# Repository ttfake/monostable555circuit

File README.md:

Monostable 555 Timer with power switch. Intended to be triggered by external digital signal

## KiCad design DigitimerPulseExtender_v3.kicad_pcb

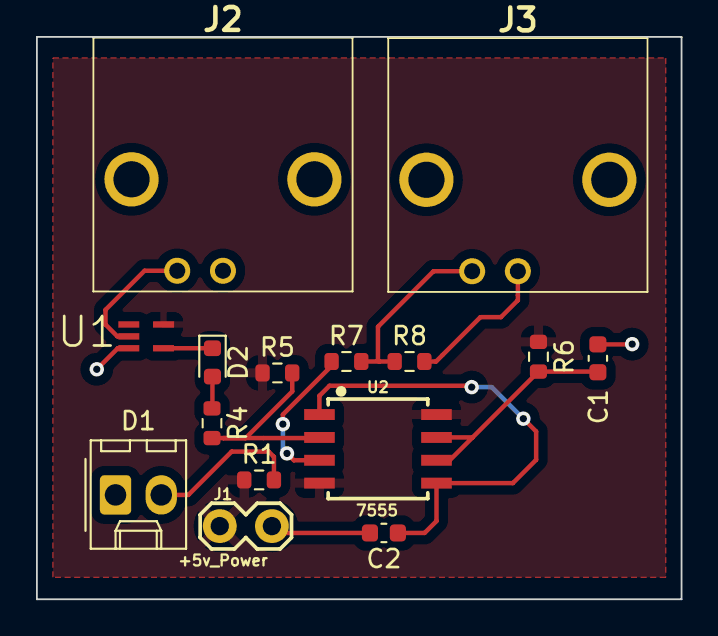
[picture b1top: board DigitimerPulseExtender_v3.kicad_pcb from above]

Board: 2 copper layers, 35.8 x 31.2 mm, 15 parts (0 on the bottom side), 11 nets.

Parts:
C1: 0.1u; C_0603_1608Metric
C2: 0.01u; C_0603_1608Metric
D1: LED; Molex_KK-254_AE-6410-02A_1x02_P2.54mm_Vertical
D2: DIODE-1N4148; D_0603_1608Metric
J1: +5v_Power; 1X02_LOCK
J2: Input_from_DS8R; 031543110RFX
J3: Output_to_DAQ; 031543110RFX
R1: 2k; R_0603_1608Metric
R4, R5, R7, R8: 1k; R_0603_1608Metric
R6: 100k; R_0603_1608Metric
U1: 74HCT1G14GW; SOT65P210X110-5N
U2: 7555; SOIC-8

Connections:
+5V: J1.1, R1.1, R5.1, R6.1, U1.5 (VCC), U2.4 (RES), U2.8 (VCC+)
GND: C1.2, C2.2, D1.1 (K), J1.2, J2.2 (Ext), J3.2 (Ext), R8.2, U1.3 (GND)
unnamed: C1.1, R6.2, U2.6 (TRE), U2.7 (DIS)
unnamed: C2.1, U2.1 (GND), U2.5 (CON)
unnamed: D1.2 (A), R1.2
unnamed: D2.A, U1.4 (Y)
unnamed: D2.B, R4.1
unnamed: R4.2, R5.2, U2.2 (TRI)
unnamed: R7.1, U2.3 (OUT)
Output_Pin_3_R7_R8: J3.1 (In), R7.2, R8.1
Pin_2_on_Inverter: J2.1 (In), U1.2 (A)

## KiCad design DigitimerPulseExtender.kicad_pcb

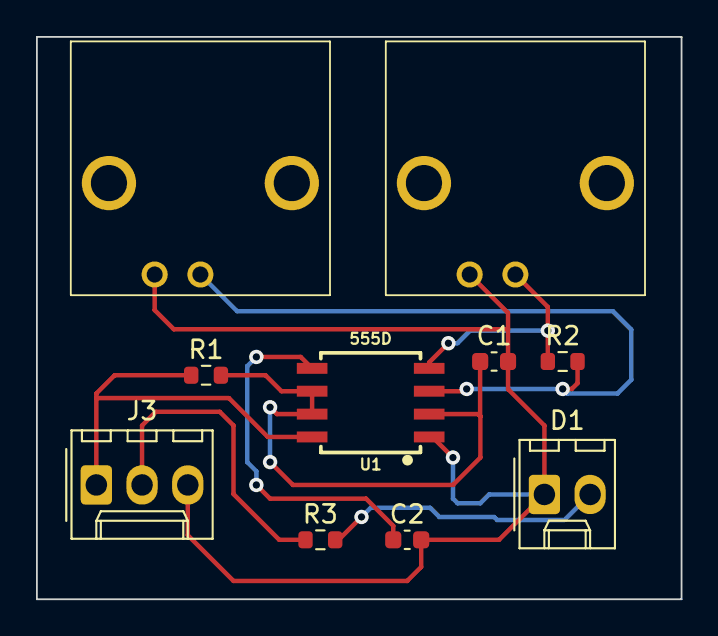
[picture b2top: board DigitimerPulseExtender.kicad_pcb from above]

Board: 2 copper layers, 35.8 x 31.2 mm, 10 parts (0 on the bottom side), 8 nets.

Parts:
C1: 0.1u; C_0603_1608Metric
C2: 0.01u; C_0603_1608Metric
D1: LED; Molex_KK-254_AE-6410-02A_1x02_P2.54mm_Vertical
J1, J2: Conn_Coaxial; 031543110RFX
J3: 6v Battery; Molex_KK-254_AE-6410-03A_1x03_P2.54mm_Vertical
R1: 100k; R_0603_1608Metric
R2: 1k; R_0603_1608Metric
R3: 2k; R_0603_1608Metric
U1: 555D; SOIC-8

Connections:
GND: C1.2, C2.2, D1.1 (K), J1.1 (In), J2.1 (In), J3.3, U1.1 (GND)
Input: J1.2 (Ext), R2.1, U1.4 (RES)
LED_PWR: J3.2, R3.1
unnamed: C1.1, R1.2, U1.2 (TRI), U1.6 (TRE), U1.7 (DIS)
unnamed: C2.1, U1.5 (CON)
unnamed: D1.2 (A), R3.2
Output: J2.2 (Ext), R2.2, U1.3 (OUT)
Power: J3.1, R1.1, U1.8 (VCC+)

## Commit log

2021-08-25 Removed hierarchical sheets. Rearranged components on PCB to minimize traces
2021-08-25 Update Gerber and Drill files
